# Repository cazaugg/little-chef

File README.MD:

# Readme of Little-Chef PCB

This is a small dev board with 3 analog inputs and 5 PWM outputs and one relay output. It is intended to control RGBW LED.

The microcontroller is an PIC18 (8 bit MIPS).

## Project description

This is where your PCB description goes. If you want to learn more about this template look at [kicad-wizard]([script/kicad-wizard.md](https://gitlab.com/christoph.zaugg/kicad-template-repo/-/blob/master/script/kicad-wizard.md)

## Workflow and project organization

- [PCB design and part libraries](pcb/pcb-info.md)
- [Documentation](pcb/doc-info.md)
- [Production](pcb/prod-info.md)

## Tools

Made with KiCad 7.

This project was setup with [kicad-wizard]([script/kicad-wizard.md](https://gitlab.com/christoph.zaugg/kicad-template-repo/-/blob/master/script/kicad-wizard.md)

***(c)2024 by cazaugg***

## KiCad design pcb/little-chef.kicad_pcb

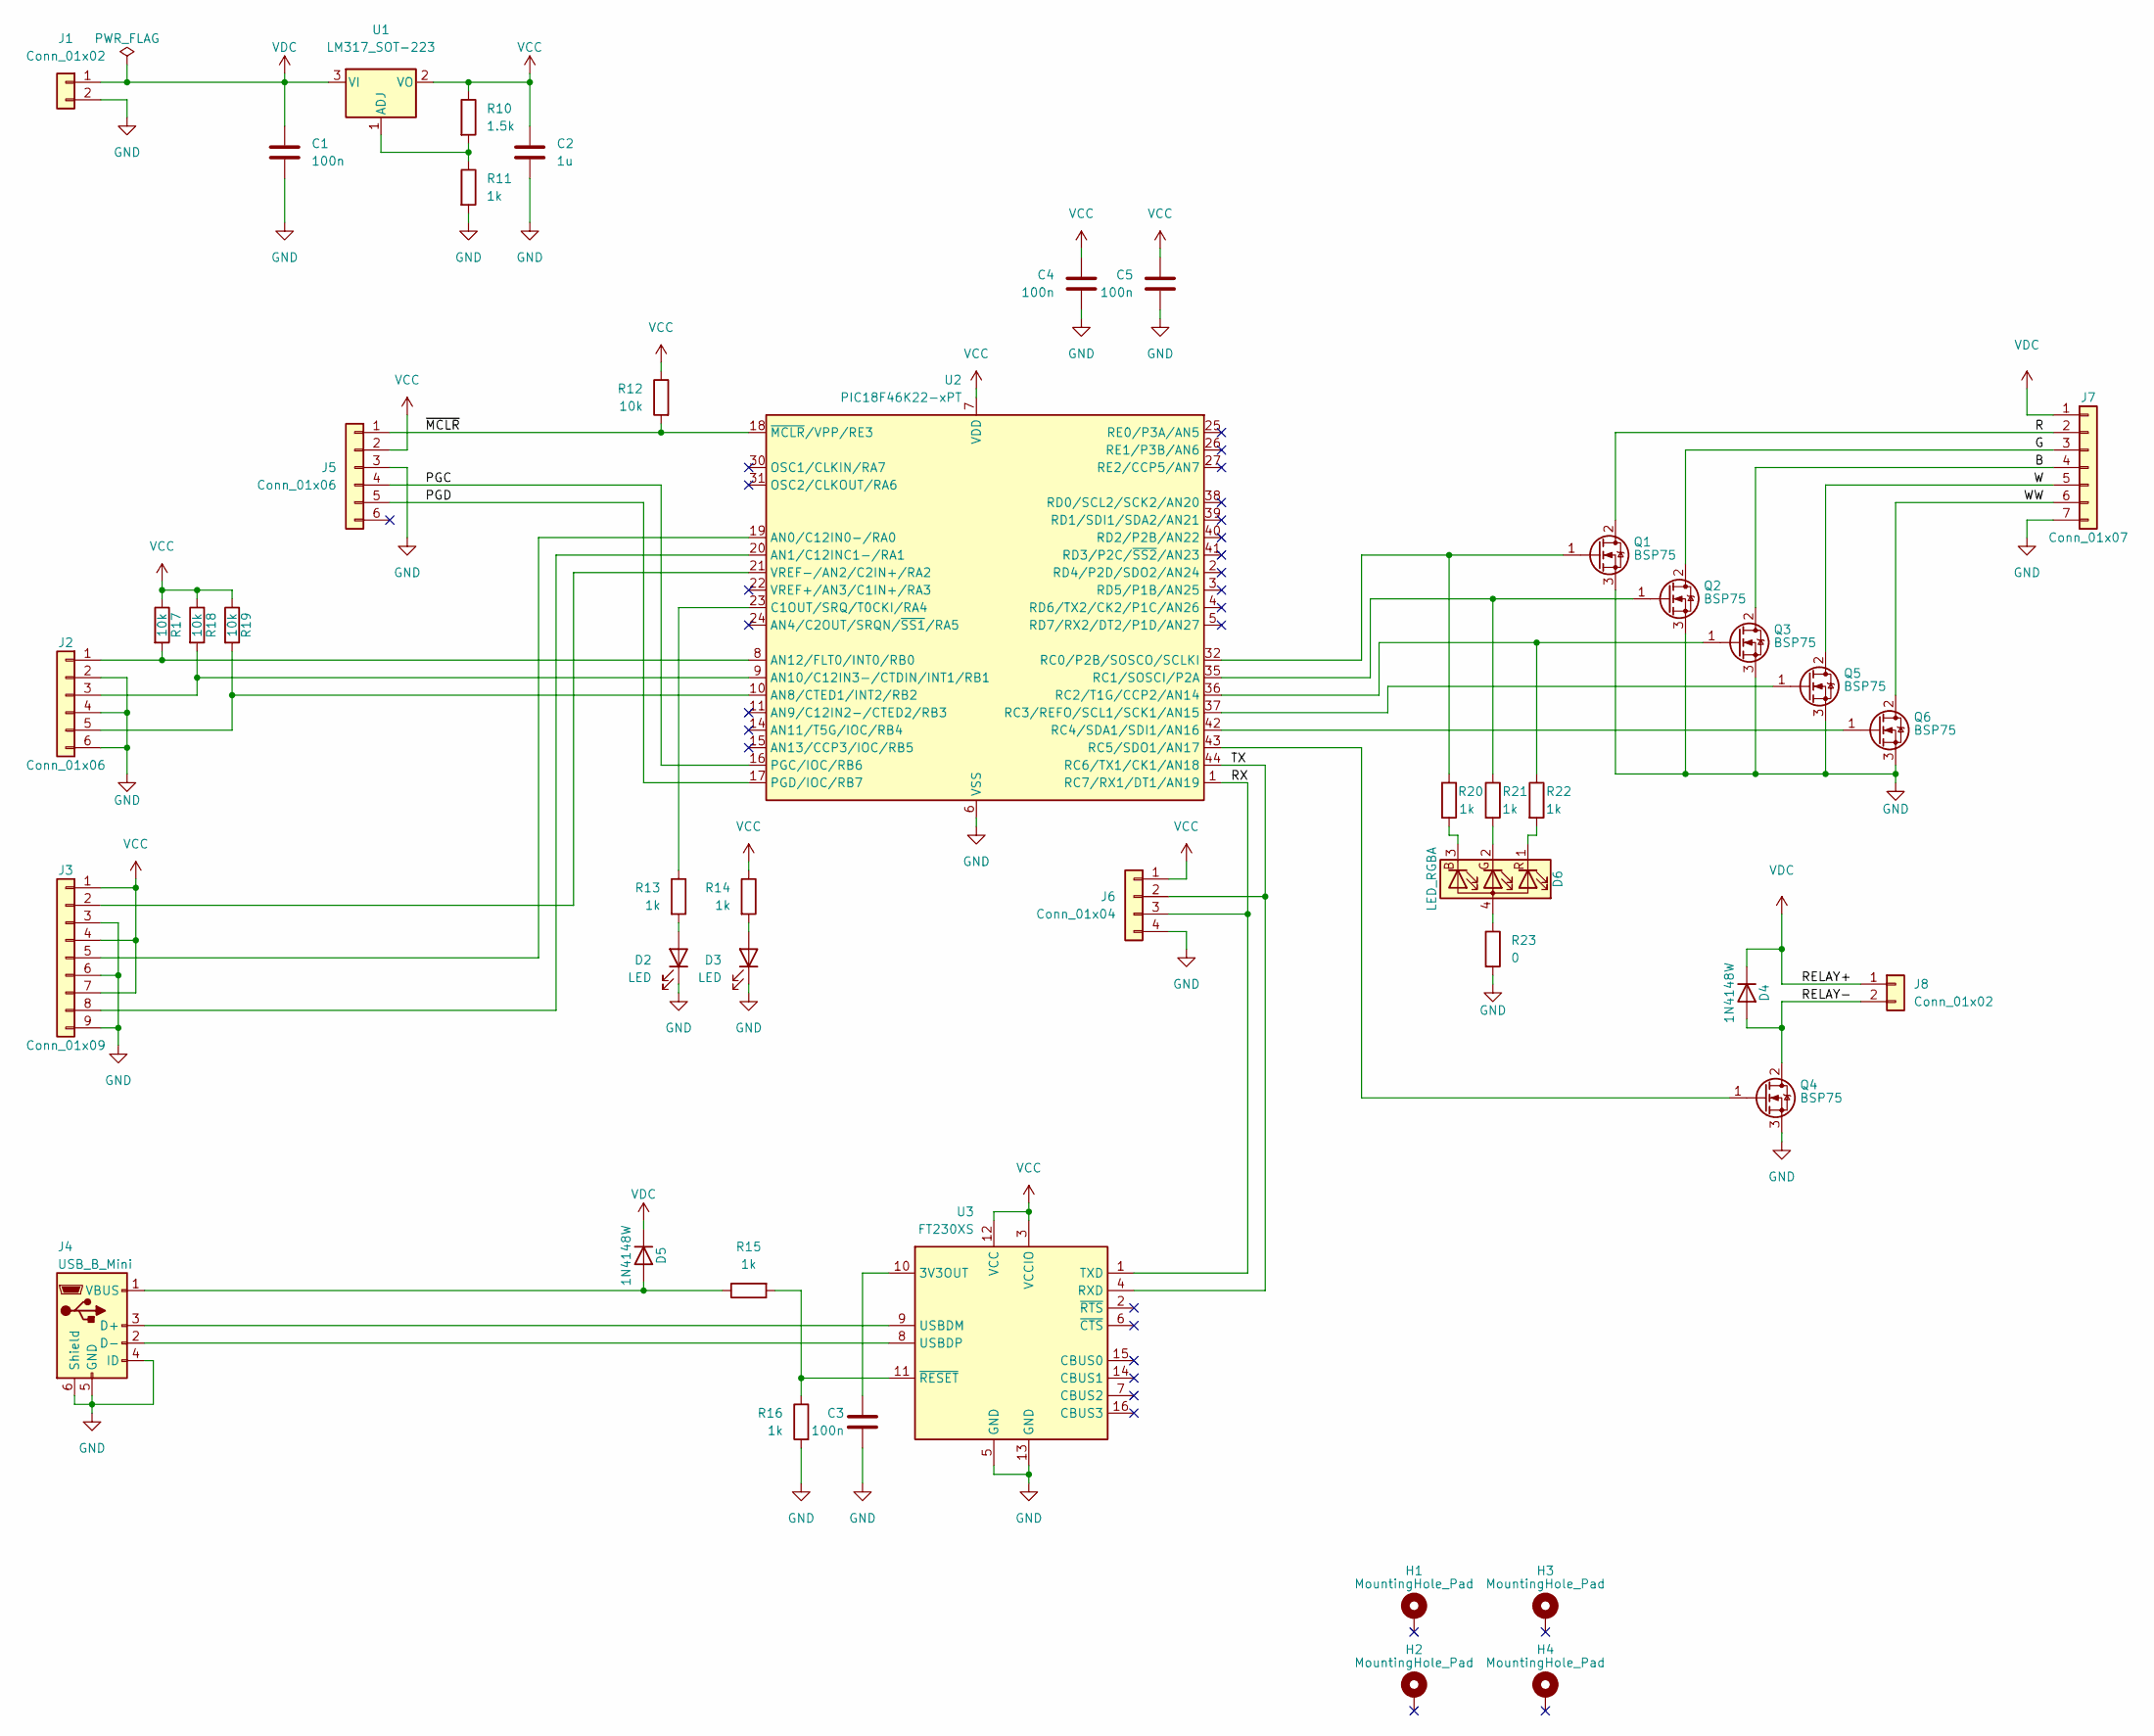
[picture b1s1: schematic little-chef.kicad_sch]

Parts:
C1, C3, C4, C5: 100n; C_0805_2012Metric
C2: 1u; C_0805_2012Metric
D2, D3: LED; LED_0805_2012Metric
D4, D5: 1N4148W; D_SOD-123
D6: LED_RGBA; LED_Cree-PLCC4_2x2mm_CW
H1, H2, H3, H4: MountingHole_Pad; MountingHole_2.7mm_M2.5_Pad_Via
J1, J8: Conn_01x02; PinHeader_1x02_P2.54mm_Vertical
J2, J5: Conn_01x06; PinHeader_1x06_P2.54mm_Vertical
J3: Conn_01x09; PinHeader_1x09_P2.54mm_Vertical
J4: USB_B_Mini; USB_Micro-B_Molex_47346-0001
J6: Conn_01x04; PinHeader_1x04_P2.54mm_Vertical
J7: Conn_01x07; PinHeader_1x07_P2.54mm_Vertical
Q1, Q2, Q3, Q4, Q5, Q6: BSP75; SOT-223-3_TabPin2
R10: 1.5k; R_0805_2012Metric
R11, R13, R14, R15, R16, R20, R21, R22: 1k; R_0805_2012Metric
R12, R17, R18, R19: 10k; R_0805_2012Metric
R23: 0; R_0805_2012Metric
U1: LM317_SOT-223; SOT-223-3_TabPin2
U2: PIC18F46K22-xPT; TQFP-44_10x10mm_P0.8mm
U3: FT230XS; SSOP-16_3.9x4.9mm_P0.635mm

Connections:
/B: J7.4, Q3.2 (D)
/G: J7.3, Q2.2 (D)
/PGC: J5.4, U2.16 (PGC/IOC/RB6)
/PGD: J5.5, U2.17 (PGD/IOC/RB7)
/R: J7.2, Q1.2 (D)
/RELAY-: D4.2 (A), J8.2, Q4.2 (D)
/RX: J6.3, U2.1 (RC7/RX1/DT1/AN19), U3.1 (TXD)
/TX: J6.2, U2.44 (RC6/TX1/CK1/AN18), U3.4 (RXD)
/W: J7.5, Q5.2 (D)
/WW: J7.6, Q6.2 (D)
/~MCLR: J5.1, R12.2, U2.18 (~MCLR/VPP/RE3)
GND: C1.2, C2.2, C3.2, C4.2, C5.2, D2.1 (K), D3.1 (K), J1.2, J2.2, J2.4, J2.6, J3.3, J3.6, J3.9, J4.4 (ID), J4.5 (GND), J4.6 (Shield), J5.3, J6.4, J7.7, Q1.3 (S), Q2.3 (S), Q3.3 (S), Q4.3 (S), Q5.3 (S), Q6.3 (S), R11.2, R16.2, R23.2, U2.6 (VSS), U2.29 (VSS), U3.5 (GND), U3.13 (GND)
unnamed: D2.2 (A), R13.2
unnamed: D3.2 (A), R14.2
unnamed: D5.2 (A), J4.1 (VBUS), R15.1
unnamed: D6.4 (A), R23.1
unnamed: D6.3 (BK), R20.2
unnamed: D6.2 (GK), R21.2
unnamed: D6.1 (RK), R22.2
unnamed: J2.1, R17.2, U2.8 (AN12/FLT0/INT0/RB0)
unnamed: J2.3, R18.2, U2.9 (AN10/C12IN3-/CTDIN/INT1/RB1)
unnamed: J2.5, R19.2, U2.10 (AN8/CTED1/INT2/RB2)
unnamed: J3.2, U2.21 (VREF-/AN2/C2IN+/RA2)
unnamed: J3.5, U2.19 (AN0/C12IN0-/RA0)
unnamed: J3.8, U2.20 (AN1/C12INC1-/RA1)
unnamed: J4.3 (D+), U3.9 (USBDM)
unnamed: J4.2 (D-), U3.8 (USBDP)
unnamed: Q1.1 (G), R20.1, U2.32 (RC0/P2B/SOSCO/SCLKI)
unnamed: Q2.1 (G), R21.1, U2.35 (RC1/SOSCI/P2A)
unnamed: Q3.1 (G), R22.1, U2.36 (RC2/T1G/CCP2/AN14)
unnamed: Q4.1 (G), U2.43 (RC5/SDO1/AN17)
unnamed: Q5.1 (G), U2.37 (RC3/REFO/SCL1/SCK1/AN15)
unnamed: Q6.1 (G), U2.42 (RC4/SDA1/SDI1/AN16)
unnamed: R10.2, R11.1, U1.1 (ADJ)
unnamed: R13.1, U2.23 (C1OUT/SRQ/T0CKI/RA4)
unnamed: C3.1, U3.10 (3V3OUT)
unnamed: R15.2, R16.1, U3.11 (~RESET)
VCC: C2.1, C4.1, C5.1, J3.1, J3.4, J3.7, J5.2, J6.1, R10.1, R12.1, R14.1, R17.1, R18.1, R19.1, U1.2 (VO), U2.7 (VDD), U2.28 (VDD), U3.3 (VCCIO), U3.12 (VCC)
VDC: C1.1, D4.1 (K), D5.1 (K), J1.1, J7.1, J8.1, U1.3 (VI)

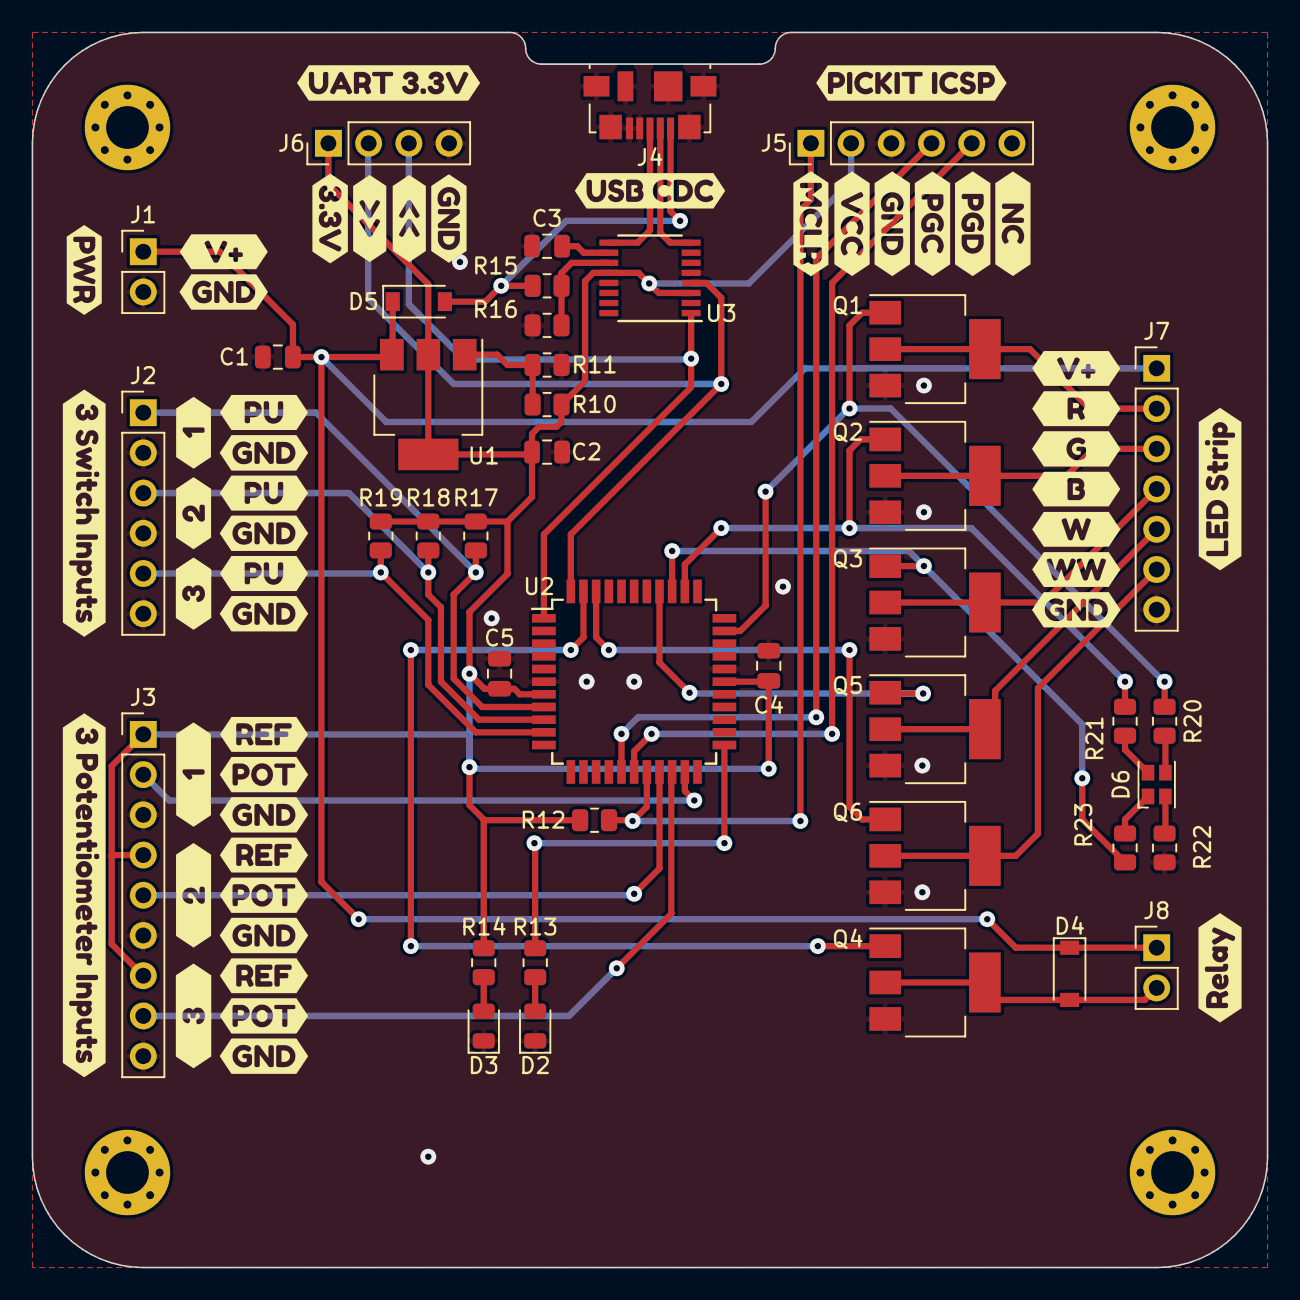
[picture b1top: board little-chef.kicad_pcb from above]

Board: 2 copper layers, 78.0 x 78.0 mm, 93 parts (0 on the bottom side), 39 nets.

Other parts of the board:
kibuzzard-63657B51, kibuzzard-63657B51#2, kibuzzard-63657B51#3, kibuzzard-63657B51#4, kibuzzard-63657B51#5, kibuzzard-63657B51#6: G***; kibuzzard-63657B51
kibuzzard-63657B69: G***; kibuzzard-63657B69
kibuzzard-63657B73: G***; kibuzzard-63657B73
kibuzzard-63657C3A: G***; kibuzzard-63657C3A
kibuzzard-63657C21: G***; kibuzzard-63657C21
kibuzzard-63657C30, kibuzzard-63657C30#2: G***; kibuzzard-63657C30
kibuzzard-63657C42: G***; kibuzzard-63657C42
kibuzzard-63657C93: G***; kibuzzard-63657C93
kibuzzard-63657CA1: G***; kibuzzard-63657CA1
kibuzzard-63657CB3: G***; kibuzzard-63657CB3
kibuzzard-63657CD2: G***; kibuzzard-63657CD2
kibuzzard-63657D2E: G***; kibuzzard-63657D2E
kibuzzard-63657D63: G***; kibuzzard-63657D63
kibuzzard-63657DA3: G***; kibuzzard-63657DA3
kibuzzard-63657DB8: G***; kibuzzard-63657DB8
kibuzzard-63657DEA, kibuzzard-63657DEA#2, kibuzzard-63657DEA#3: G***; kibuzzard-63657DEA
kibuzzard-63657E0E, kibuzzard-63657E0E#2, kibuzzard-63657E0E#3: G***; kibuzzard-63657E0E
kibuzzard-63657E02, kibuzzard-63657E02#2, kibuzzard-63657E02#3: G***; kibuzzard-63657E02
kibuzzard-63657E67: G***; kibuzzard-63657E67
kibuzzard-63657E77: G***; kibuzzard-63657E77
kibuzzard-63657E92: G***; kibuzzard-63657E92
kibuzzard-63657EAB: G***; kibuzzard-63657EAB
kibuzzard-63657EB2: G***; kibuzzard-63657EB2
kibuzzard-63657EBB: G***; kibuzzard-63657EBB
kibuzzard-63657FD1: G***; kibuzzard-63657FD1
kibuzzard-636580FF: G***; kibuzzard-636580FF
kibuzzard-636588B1: G***; kibuzzard-636588B1
kibuzzard-636588D1: G***; kibuzzard-636588D1
kibuzzard-636588DA: G***; kibuzzard-636588DA
kibuzzard-636588E4: G***; kibuzzard-636588E4
kibuzzard-6365804D, kibuzzard-6365804D#2: G***; kibuzzard-6365804D
kibuzzard-63658200, kibuzzard-63658200#2, kibuzzard-63658200#3: G***; kibuzzard-63658200
kibuzzard-63658897: G***; kibuzzard-63658897

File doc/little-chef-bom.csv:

"Source:","G:\Electronics\Hardware\little-rgbw\pcb\little-chef.kicad_sch"
"Date:","01.01.2024 15:31:51"
"Tool:","Eeschema 7.0.10"
"Generator:","C:\Program Files\KiCad\7.0\bin\scripting\plugins/bom_csv_grouped_by_value_with_fp.py"
"Component Count:","41"
"Ref","Qnty","Value","Cmp name","Footprint","Description","Vendor","DNP"
"C1, C3, C4, C5","4","100n","C","Capacitor_SMD:C_0805_2012Metric","Unpolarized capacitor","",""
"C2","1","1u","C","Capacitor_SMD:C_0805_2012Metric","Unpolarized capacitor","",""
"D2, D3","2","LED","LED","LED_SMD:LED_0805_2012Metric","Light emitting diode","",""
"D4, D5","2","1N4148W","1N4148W","Diode_SMD:D_SOD-123","75V 0.15A Fast Switching Diode, SOD-123","",""
"D6","1","LED_RGBA","LED_RGBA","LED_SMD:LED_Cree-PLCC4_2x2mm_CW","RGB LED, red/green/blue/anode","",""
"J1, J8","2","Conn_01x02","Conn_01x02","Connector_PinHeader_2.54mm:PinHeader_1x02_P2.54mm_Vertical","Generic connector, single row, 01x02, script generated (kicad-library-utils/schlib/autogen/connector/)","",""
"J2, J5","2","Conn_01x06","Conn_01x06","Connector_PinHeader_2.54mm:PinHeader_1x06_P2.54mm_Vertical","Generic connector, single row, 01x06, script generated (kicad-library-utils/schlib/autogen/connector/)","",""
"J3","1","Conn_01x09","Conn_01x09","Connector_PinHeader_2.54mm:PinHeader_1x09_P2.54mm_Vertical","Generic connector, single row, 01x09, script generated (kicad-library-utils/schlib/autogen/connector/)","",""
"J4","1","USB_B_Mini","USB_B_Mini","Connector_USB:USB_Micro-B_Molex_47346-0001","USB Mini Type B connector","",""
"J6","1","Conn_01x04","Conn_01x04","Connector_PinHeader_2.54mm:PinHeader_1x04_P2.54mm_Vertical","Generic connector, single row, 01x04, script generated (kicad-library-utils/schlib/autogen/connector/)","",""
"J7","1","Conn_01x07","Conn_01x07","Connector_PinHeader_2.54mm:PinHeader_1x07_P2.54mm_Vertical","Generic connector, single row, 01x07, script generated (kicad-library-utils/schlib/autogen/connector/)","",""
"Q1, Q2, Q3, Q4, Q5, Q6","6","BSP75","BSP89","Package_TO_SOT_SMD:SOT-223-3_TabPin2","0.35A Id, 240V Vds, N-Channel Enhancement Mode MOSFET, SOT-223","",""
"R10","1","1.5k","R","Resistor_SMD:R_0805_2012Metric","Resistor","",""
"R11, R13, R14, R15, R16, R20, R21, R22","8","1k","R","Resistor_SMD:R_0805_2012Metric","Resistor","",""
"R12, R17, R18, R19","4","10k","R","Resistor_SMD:R_0805_2012Metric","Resistor","",""
"R23","1","0","R","Resistor_SMD:R_0805_2012Metric","Resistor","",""
"U1","1","LM317_SOT-223","LM317_SOT-223","Package_TO_SOT_SMD:SOT-223-3_TabPin2","1.5A 35V Adjustable Linear Regulator, SOT-223","",""
"U2","1","PIC18F46K22-xPT","PIC18F46K22-xPT","Package_QFP:TQFP-44_10x10mm_P0.8mm","64K Flash, 3.5K RAM, 1K EEPROM PIC18 Microcontroller ADC PWM SPI I2C USART in TQFP44 package","",""
"U3","1","FT230XS","FT230XS","Package_SO:SSOP-16_3.9x4.9mm_P0.635mm","Full Speed USB to Basic UART, SSOP-16","",""

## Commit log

2022-07-04 Setup repo.
2023-01-06 Rename project
2024-01-02 Add first prototype
